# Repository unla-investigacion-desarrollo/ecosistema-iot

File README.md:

# 📡 Proyecto IoT: Monitoreo de Temperatura y Humedad

## 🧠 Etapa de Investigación

Antes de desarrollar el sistema final, realizamos una etapa de exploración donde investigamos y experimentamos con las siguientes tecnologías:

- **Sensor de Movimiento**: exploramos sensores básicos para detección de presencia, como base para entender la comunicación entre hardware y software.
- **ESP32**: microcontrolador Wi-Fi/Bluetooth que usamos para adquirir lecturas desde sensores y transmitirlas de forma inalámbrica.
- **MQTT (Mosquitto)**: protocolo de mensajería ligero ideal para IoT; aprendimos a usar Mosquitto como broker MQTT para intermediar entre dispositivos.
- **Node-RED**: plataforma visual de flujo para integración entre sistemas. Nos permitió trabajar con MQTT y hacer pruebas rápidas.
- **NestJS y GraphQL (Apollo Server)**: framework backend robusto y moderno que usamos para construir APIs modulares, escalables y tipadas.
- **MongoDB + Mongoose**: base de datos NoSQL flexible y orientada a documentos, utilizada con Mongoose para facilitar la conexión desde Node.js.

Esta fase fue clave para entender cómo se comunican los distintos componentes y evaluar qué tan bien se integran en un ecosistema IoT moderno.

---

## 🚀 Proyecto Final: Sistema de Monitoreo IoT

### 🎯 Objetivo

Diseñar e implementar un sistema completo de monitoreo en tiempo real de temperatura y humedad, desde el hardware hasta la visualización de datos en una interfaz web.

### 🔄 Flujo del Sistema

1. **Adquisición de Datos**  
   El sensor **DHT11** conectado al **ESP32** mide temperatura y humedad.

2. **Transmisión vía MQTT**  
   El ESP32 publica los datos en un **broker Mosquitto** mediante el protocolo **MQTT**.

3. **Procesamiento en Node-RED**  
   Un flujo en **Node-RED** se suscribe al topic MQTT, toma los datos y realiza una petición **GraphQL** a la API para registrar cada medición.

4. **API NestJS con GraphQL**  
   La API construida en **NestJS + Apollo Server** maneja, entre otros métodos:
   - Registro de mediciones.
   - Consulta de la última medición.
   - Promedios de las últimas *n* mediciones.
   - Consulta de las últimas *n* mediciones.
   - Inserción de una nueva medición tomada por el sensor.

   Toda la información es almacenada en **MongoDB Atlas** utilizando **Mongoose**.

5. **Visualización Web (Next.js)**  
   El frontend hecho en **Next.js** muestra:
   - Dos gráficos tipo **gauge** (usando `react-gauge-chart`) con:
     - Última medición de temperatura y humedad.
     - Promedio de las últimas 10 mediciones.
   - Una **tabla con las últimas 10 mediciones**, incluyendo:
     - Fecha y hora
     - Temperatura
     - Humedad

---

## 🧱 Tecnologías Utilizadas

| Componente        | Tecnología             |
|------------------|------------------------|
| Sensor            | DHT11                  |
| Microcontrolador  | ESP32                  |
| Comunicación      | MQTT (Broker Mosquitto)|
| Orquestación      | Node-RED               |
| Backend           | NestJS + GraphQL (Apollo Server) |
| Base de datos     | MongoDB Atlas + Mongoose |
| Frontend          | Next.js + React Gauge Chart |

---

## 📊 Principales funcionalidades de la API

- `traerMedicionActual()`: Última medición registrada.
- `traerPromedioTemperatura(n)`: Promedio de temperatura de las últimas *n* mediciones.
- `traerPromedioHumedad(n)`: Promedio de humedad de las últimas *n* mediciones.
- `traerUltimasMediciones(n)`: Lista de las últimas *n* mediciones.
- `agregarMedicon(fechaHora, temperatura, humedad)`: Persistencia de la medición tomada por el sensor.

---

## 💡 Conclusiones

Este proyecto nos permitió no solo entender el funcionamiento individual de tecnologías modernas relacionadas con el IoT y el desarrollo web, sino también integrarlas en una solución real, escalable y visualmente atractiva.

Durante el proceso, pasamos de la teoría a la práctica, aprendiendo sobre:

- Integración de hardware y software.
- Comunicación en tiempo real mediante MQTT.
- Diseño de APIs modernas con GraphQL.
- Modelado y consulta de datos en MongoDB.
- Visualización efectiva de datos en una app web.

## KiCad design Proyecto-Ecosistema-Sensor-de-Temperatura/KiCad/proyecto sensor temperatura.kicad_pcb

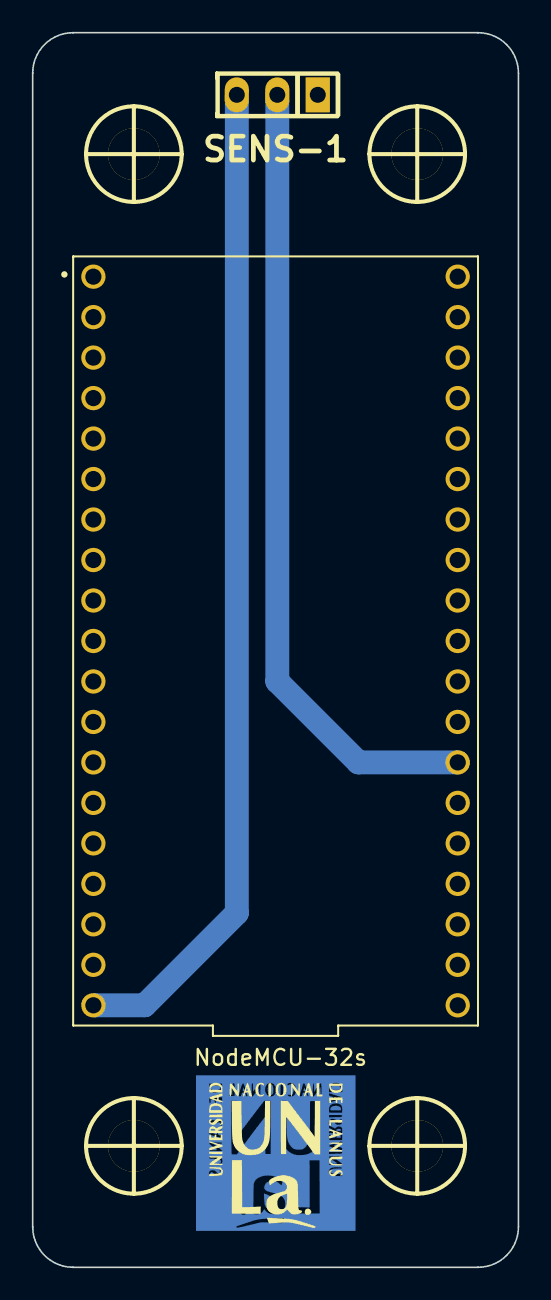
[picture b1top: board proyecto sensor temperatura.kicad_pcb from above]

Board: 2 copper layers, 30.5 x 77.5 mm, 8 parts (0 on the bottom side), 3 nets.

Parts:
H1, H2, H3, H4: MountingHole; Separador_M3_5mm
Logo UNLa: LOGO; logoUnlaFootprint
Micro_controlador1: NodeMCU-32s; MODULE_NODEMCU-32S
SENS-1: DHT11; Pin_Header_3
UNLa Logo Invertido: LOGO; logoUnlaFootprintNoNegativeInvertida

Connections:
+5V: Micro_controlador1.19 (5V), SENS-1.3 (GND)
/Data: Micro_controlador1.26 (IO4), SENS-1.2 (DAT)
GND: Micro_controlador1.14 (GND), Micro_controlador1.32 (GND), Micro_controlador1.38 (GND), SENS-1.1 (VCC)

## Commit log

2024-10-31 Primeros pasos en la construccion de la API
2024-11-04 Documentación de la descripción y guía de instalación de la API.
2024-11-27 remove node_modules
2024-11-27 re order project
2024-11-27 some fixes
2024-11-27 Subimos la conversión de los esquemas a TS
2024-11-27 Subimos los esquemas y los resolvers
2024-11-27 re order structure
2024-11-27 Subimos los datos iniciales con los que trabaja la API
2024-11-27 Subimos la base del proyecto
2024-11-27 Subimos los archivos que permiten levantar el servidor y consumir la API
2024-11-27 Primeros pasos en API con Apollo Server
2024-11-27 Creamos un readme con la descripción de la API y una guía de instalación de la misma.
2024-11-27 re order repo
2024-11-27 Pequeña corrección sobre el texto.
2024-11-27 Implementaciones de la API
2024-11-27 Pequeña corrección sobre un comando a ejecutar en la instalación de la API.
2024-11-27 final-fix
2024-12-13 Configuración base del proyecto
2024-12-13 Código de la API
2024-12-13 Diagramas de Node-RED
2024-12-13 Configuración para levantar la API y Node-RED con Docker
2024-12-13 Descripción y explicación de instalación y uso del proyecto
2024-12-13 Corrección sobre la ubicación del readme
2024-12-13 Removemos el readme dentro del proyecto
2024-12-13 El readme acá no va
2024-12-13 Ahora sí está bien ubicado :)
2024-12-13 Configuración de los diagramas de Node-RED
2024-12-13 Descripción y explicación de instalación y uso
2024-12-13 Corrección sobre el archivo
2025-03-24 Initial commit from Create Next App
2025-03-24 adding-lock
2025-03-24 adding GaugeChart and Mock API
2025-03-25 Configuraciones base y primeras implementaciones de la API
2025-03-25 Implementación de queries y mutations
2025-03-28 Agregamos algunas dependencias al proyecto, principalmente para la incorporación de persistencia
2025-03-28 Reestructuración del proyecto, refactorización e implementación de nuevos métodos para incorporar persistencia
2025-04-01 Modificiones e implementaciones de endpoints
2025-04-02 Optimizacion y nuevos endpoints
2025-04-02 Incorporamos CORS para permitir solicitudes del front
2025-04-02 Correcciones de estilo del código fuente
2025-04-03 Encarpetación del proyecto
2025-04-03 Incorporamos la dependencia de Apollo Client para interactuar con la API
2025-04-03 Reemplazamos el mock de la API por la desarrollada y configuramos la conexión para consumir los endpoints
2025-04-04 Actualización del readme con la descripción del proyecto y guía de instalación
2025-04-06 Reemplazo de README.md
2025-04-06 Agregamos diagramado para conexión de componentes
2025-04-07 Codigo Inicial del ESP32
2025-04-07 nuevo nombre proyecto investigar tecnologias
2025-04-07 sacando carpeta del proyecto anterior, porque tenia un .git y redirecionaba al mismo proyecto
2025-04-07 correccion del .git
2025-04-07 Removemos el .gitignore general
2025-04-07 Subimos el código de la API
2025-04-07 Subimos el código del diagrama de Node-RED
2025-04-07 Subimos el código del dashboard
2025-04-08 Modificaciones sobre los readmes de la API y el dashboard
2025-04-08 Redactamos el readme relacionado al desarrollo en Node-RED
2025-04-08 Detallamos el paso a paso de la conexión con el broker MQTT
2025-04-08 Agregamos un estilo para los gráficos gauge
2025-04-08 Removemos la animación de los gráficos gauge
2025-04-08 Redactamos el readme general del proyecto
2025-04-08 Actualización del readme general
2025-04-08 ignorar carpeta ´levantar back´
2025-04-08 agregar docker de mosquitto
2025-04-09 se testeo todo y se comento el codigo del esp32
2025-04-09 documentacion del proyecto de sensor de temperatura
2025-05-12 ultimos cambios KiCad
2025-05-13 Importar contenido de proyecto-sensor-temperatura-humedad a main
2025-07-08 configuracion inicial Spring Boot
2025-07-08 dependencias agregadas
